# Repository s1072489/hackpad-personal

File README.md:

# Hackclub Hackpad
My design for the Hackclub Hackpad! Although honestly now that I think about it... it's really just a de-constructed keyboard  

Hope it's still okay though.

Front:  
  
Back:  

# Acknowledgements:
- Images from [HackClub](https://hackclub.com/brand), and [Github](https://github.com/logos)  
- MX switches footprints from [sszczep/kicad-libraries](https://github.com/sszczep/kicad-libraries/tree/master)

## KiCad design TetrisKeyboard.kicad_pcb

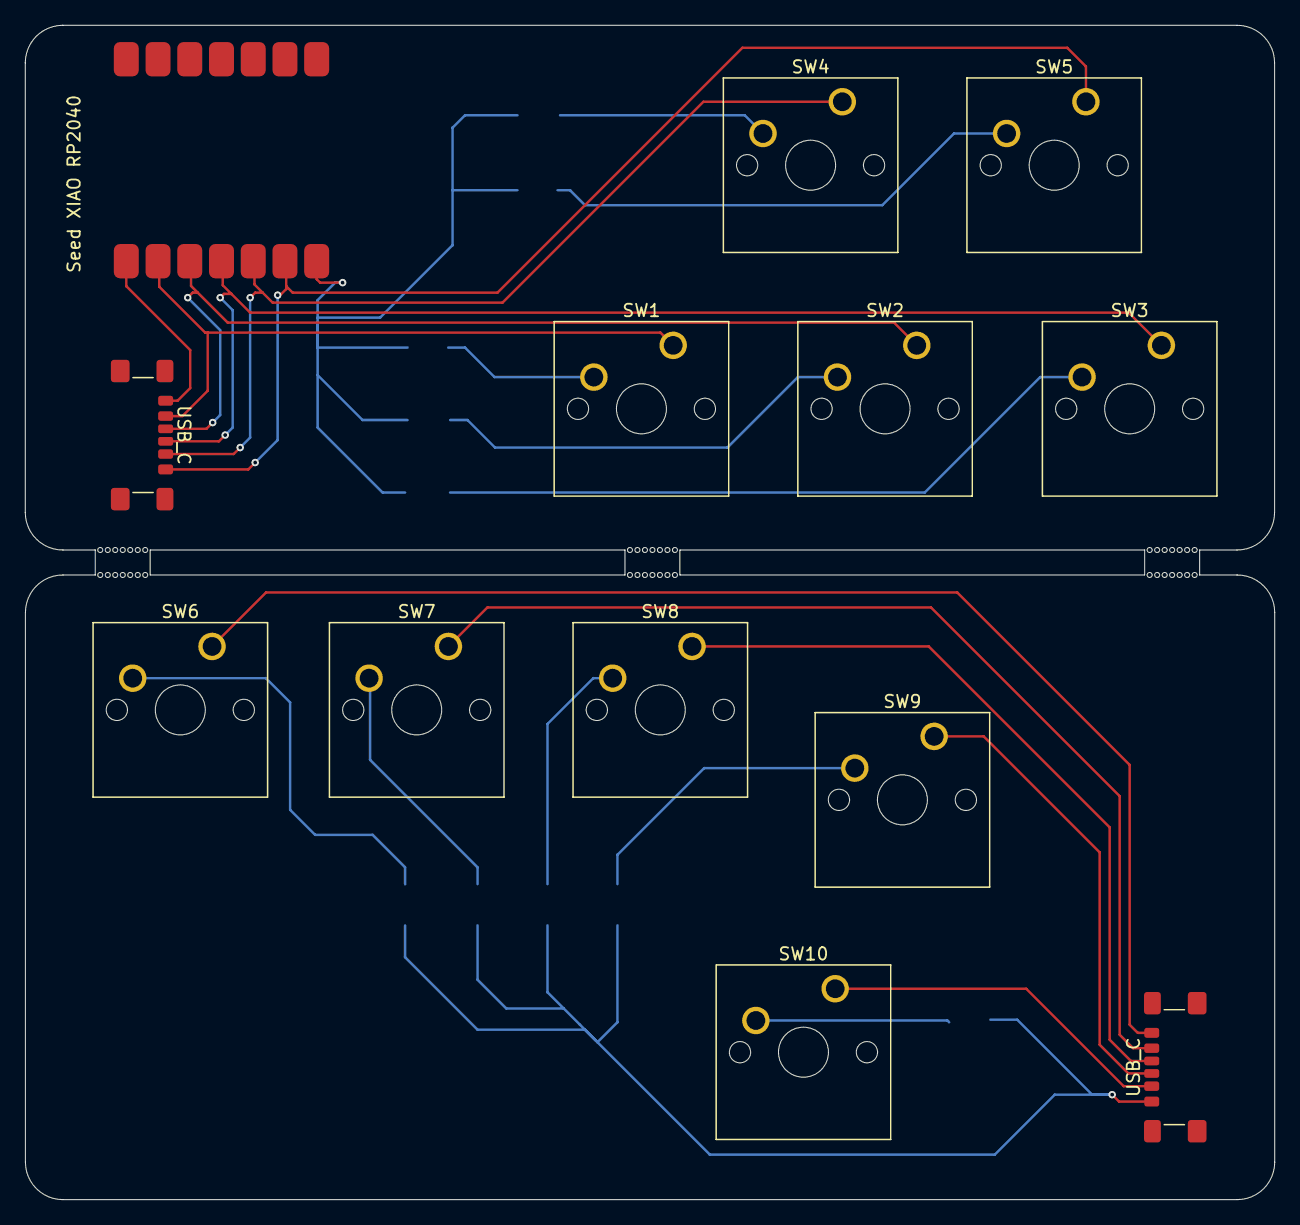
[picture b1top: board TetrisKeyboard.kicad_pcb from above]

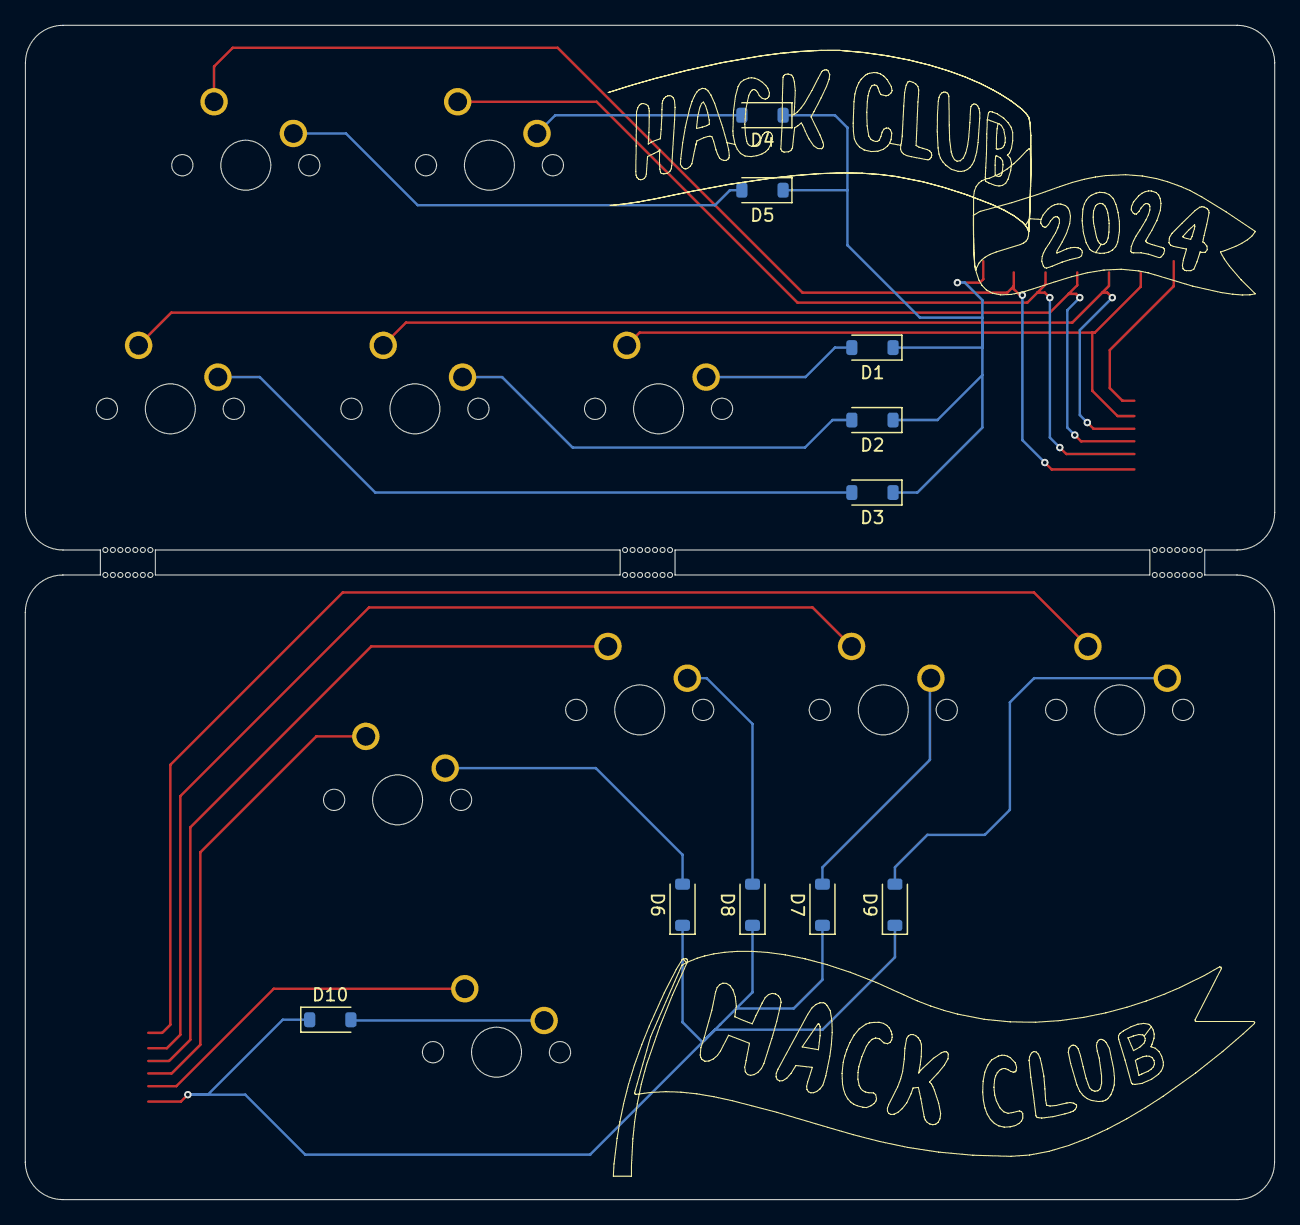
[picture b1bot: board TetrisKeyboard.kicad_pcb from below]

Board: 2 copper layers, 100.0 x 94.0 mm, 23 parts (10 on the bottom side), 13 nets.

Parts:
D1, D2, D3, D4, D5, D6, D7, D8, D9, D10: 1N4148W; D_SOD-123
SW1, SW2, SW3, SW4, SW5, SW6, SW7, SW8, SW9, SW10: SW_Cherry_MX_1.00u_PCB
Seed XIAO RP2040: MOUDLE14P-SMD-2.54-21X17.8MM
USB_C: USB_C_Receptacle_GCT_USB4135-GF-A_6P_TopMnt_Horiz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; USB_C_Receptacle_GCT_USB4135-GF-A_6P_TopMnt_Horizontal
USB_C#2: USB_C_Receptacle_GCT_USB4135-GF-A_6P_TopMnt_Horiz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; USB_C_Receptacle_GCT_USB4135-GF-A_6P_TopMnt_Horizontal

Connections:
Col1: SW1.1, Seed XIAO RP2040.2, USB_C.B9
Col1-B: SW10.1, USB_C#2.B9
Col2: SW2.1, Seed XIAO RP2040.3, USB_C.A5
Col2-B: SW9.1, USB_C#2.A5
Col3: SW3.1, Seed XIAO RP2040.4, USB_C.B5
Col3-B: SW8.1, USB_C#2.B5
Col4: SW4.1, Seed XIAO RP2040.5, USB_C.A9
Col4-B: SW7.1, USB_C#2.A9
Col5: SW5.1, Seed XIAO RP2040.6, USB_C.A12
Col5-B: SW6.1, USB_C#2.A12
Row1: D1.1, D1.2, D2.1, D2.2, D3.1, D3.2, D4.1, D4.2, D5.1, D5.2, SW1.2, SW2.2, SW3.2, SW4.2, SW5.2, Seed XIAO RP2040.7
Row2: Seed XIAO RP2040.1, USB_C.B12
Row2-B: D6.1, D6.2, D7.1, D7.2, D8.1, D8.2, D9.1, D9.2, D10.1, D10.2, SW6.2, SW7.2, SW8.2, SW9.2, SW10.2, USB_C#2.B12

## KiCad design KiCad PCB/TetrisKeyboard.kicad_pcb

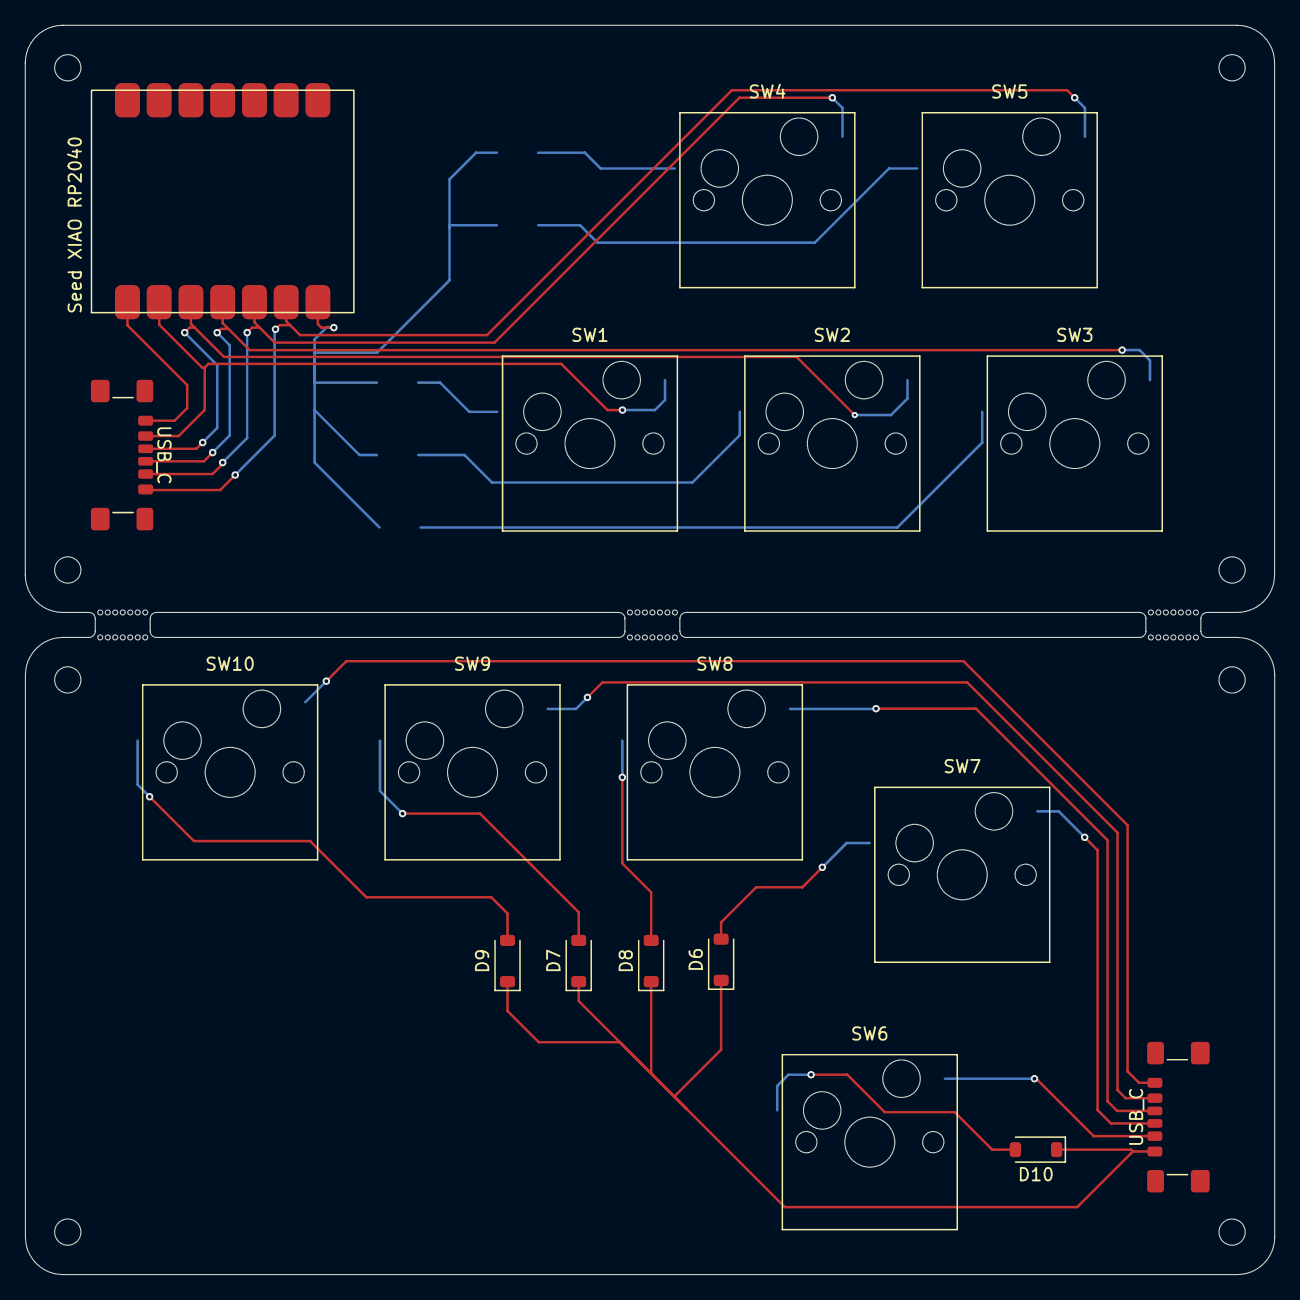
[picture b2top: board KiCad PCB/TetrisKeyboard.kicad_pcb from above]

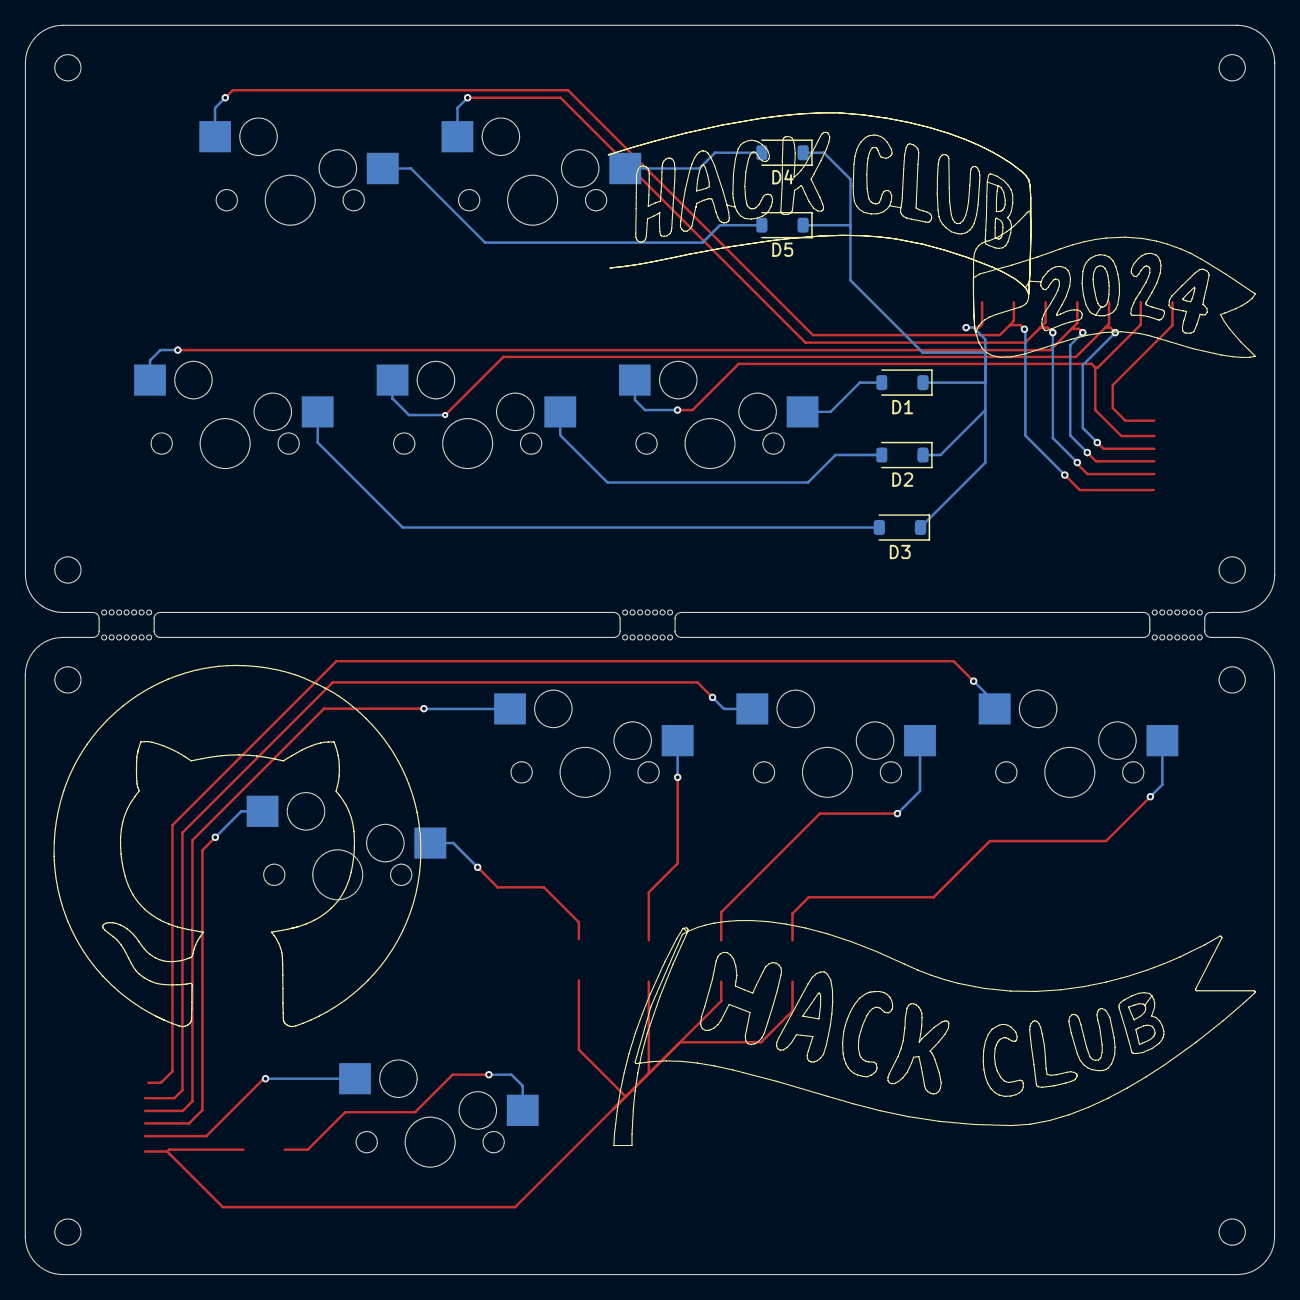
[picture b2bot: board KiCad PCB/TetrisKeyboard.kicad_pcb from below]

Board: 2 copper layers, 100.0 x 100.0 mm, 29 parts (5 on the bottom side), 13 nets.

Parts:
2.1mm, 2.1mm#2, 2.1mm#3, 2.1mm#4, 2.1mm#5, 2.1mm#6: MountingHole_2.1mm
D1, D2, D3, D4, D5, D6, D7, D8, D9, D10: 1N4148W; D_SOD-123
SW1, SW2, SW3, SW4, SW5, SW6, SW7, SW8, SW9, SW10: CherryMX_1.00u_KailhSocket
Seed XIAO RP2040: MOUDLE14P-SMD-2.54-21X17.8MM
USB_C: USB_C_Receptacle_GCT_USB4135-GF-A_6P_TopMnt_Horiz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; USB_C_Receptacle_GCT_USB4135-GF-A_6P_TopMnt_Horizontal
USB_C#2: USB_C_Receptacle_GCT_USB4135-GF-A_6P_TopMnt_Horiz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; USB_C_Receptacle_GCT_USB4135-GF-A_6P_TopMnt_Horizontal

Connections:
Col1: SW1.2, Seed XIAO RP2040.2, USB_C.B9
Col1-B: SW6.2, USB_C#2.B9
Col2: SW2.2, Seed XIAO RP2040.3, USB_C.A5
Col2-B: SW7.2, USB_C#2.A5
Col3: SW3.2, Seed XIAO RP2040.4, USB_C.B5
Col3-B: SW8.2, USB_C#2.B5
Col4: SW4.2, Seed XIAO RP2040.5, USB_C.A9
Col4-B: SW9.2, USB_C#2.A9
Col5: SW5.2, Seed XIAO RP2040.6, USB_C.A12
Col5-B: SW10.2, USB_C#2.A12
Row1: D1.1, D1.2, D2.1, D2.2, D3.1, D3.2, D4.1, D4.2, D5.1, D5.2, SW1.1, SW2.1, SW3.1, SW4.1, SW5.1, Seed XIAO RP2040.7
Row2: Seed XIAO RP2040.1, USB_C.B12
Row2-B: D6.1, D6.2, D7.1, D7.2, D8.1, D8.2, D9.1, D9.2, D10.1, D10.2, SW6.1, SW7.1, SW8.1, SW9.1, SW10.1, USB_C#2.B12

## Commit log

2024-09-21 Initial Upload
2024-09-22 Update file structure and pcb
2024-09-22 Change to hot-swappable sockets, added mounting holes
2024-09-22 Clean up sszczep Lib
2024-09-22 Fix 3D models and clean up unused footprints
2024-09-22 Fix broken link in README.md
2024-09-22 Remove unused file
2024-09-22 Update socket footprint and add versioning
2024-09-23 Update TetrisKeyboard.kicad_pcb
    Fix RP2040 covering mounting hole
2024-09-23 Update TetrisKeyboard.kicad_pcb
    Fix text on wrong layer and slight movement of keys
2024-10-03 Upload firmware
2024-10-03 Update Kicad
2024-10-03 Add 3D models
